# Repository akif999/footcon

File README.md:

# Footcon

Footcon is a USB device that send keyboard-like keys to a PC with a foot pedal.

## Hardware

The hardware composition is based on References 1. (Japanese website).  

Composition detail is below:

* Housing
    * TAKACHI YM-100
* Substrate
    * [footcon](https://github.com/akif999/footcon/tree/main/kicad/footcon)
    * [gerber](https://github.com/akif999/footcon/tree/main/gerber)
        * A board can be made using the files in this folder
* Foot pedal
    * [YAMAHA FC-5](https://jp.yamaha.com/products/music_production/accessories/fc5/index.html)
* Microcontroller board
    * [Seeed Studio XIAO SAMD21](https://lab.seeed.co.jp/entry/2022/08/19/120000)

## Software

The software consists of the following two items:

* Firmware
    * Software to detect pedal input and send key to PC
        * Write to XIAO
* Config GUI
    * Software for setting up Footcon
        * Works standalone on PC

### Firmware

Build and use the tinygo project under [firmware](https://github.com/akif999/footcon/tree/main/firmware).  

```
$ cd firmware
$ tinygo flash -target=xiao
```

* Requirement
    * Tinygo 0.27 or later

### Config GUI(WIP)

**Configuration GUI will be implemented as soon as Tinygo0.28.0 is released.**

Build [config_gui](https://github.com/akif999/footcon/tree/main/config_gui) and below to create an executable and use it.

```
$ cd config_gui
$ go build -o config_gui
$ ./config_gui
```

* Requirement
    * Go 1.19 or later

## References

1. https://qiita.com/carcon999/items/9b57537cadbfd3c13cf0

## License

This project is licensed under the MIT license.

## Author

Akifumi Kitabatake (a.k.a akif or akif999)

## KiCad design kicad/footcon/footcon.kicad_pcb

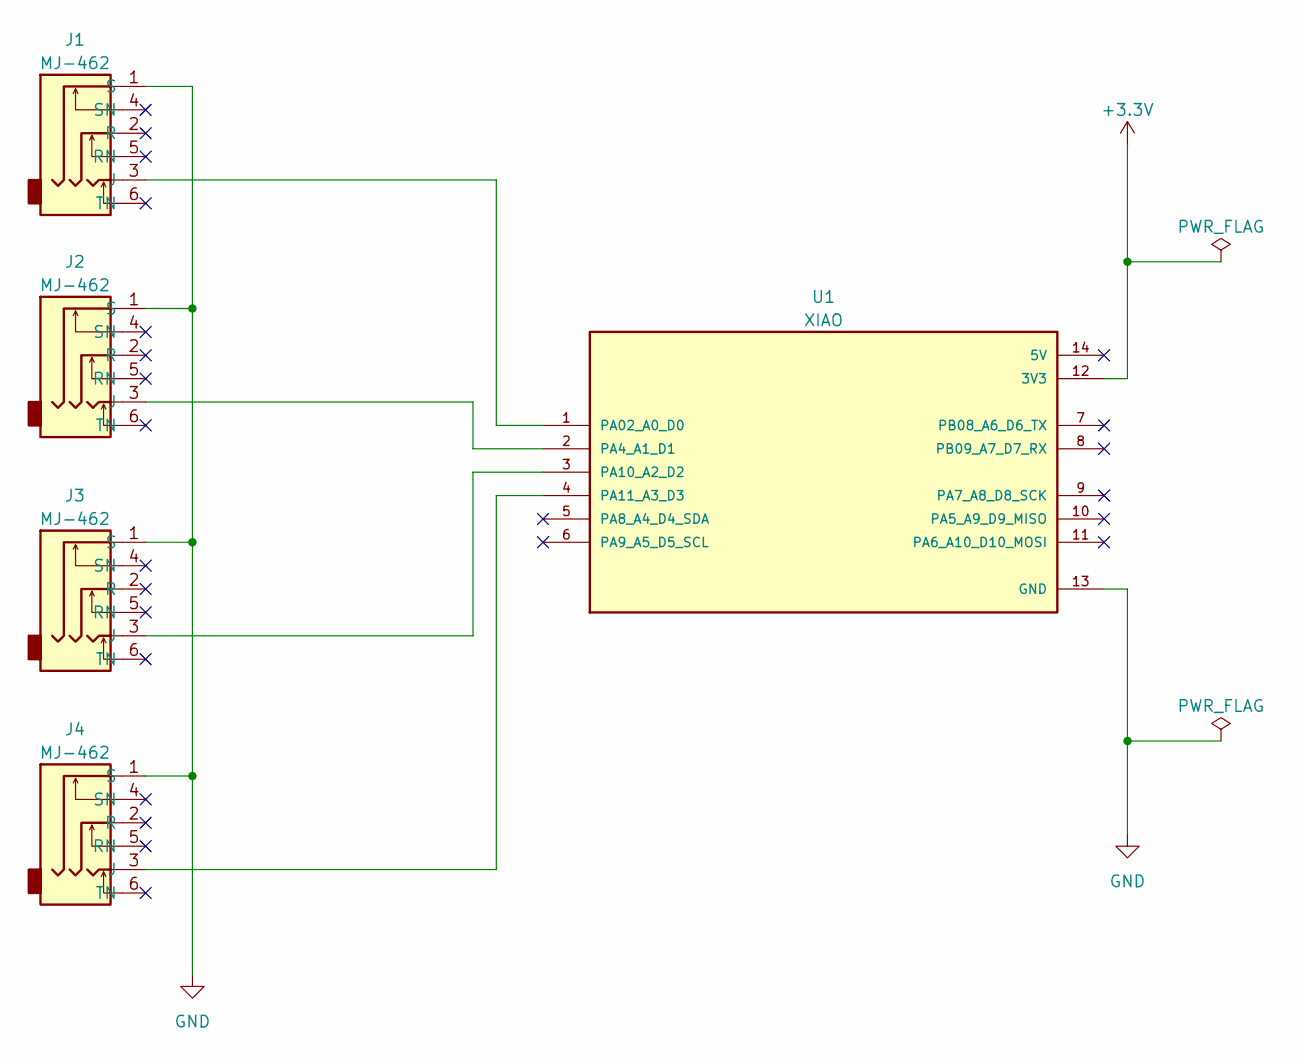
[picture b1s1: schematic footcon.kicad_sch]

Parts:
J1, J2, J3, J4: MJ-462
U1: XIAO; MODULE_102010388; PARTREV N/A

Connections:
+3.3V: U1.12 (3V3)
GND: J1.1 (S), J2.1 (S), J3.1 (S), J4.1 (S), U1.13 (GND)
unnamed: J1.3 (J), U1.1 (PA02_A0_D0)
unnamed: J2.3 (J), U1.2 (PA4_A1_D1)
unnamed: J3.3 (J), U1.3 (PA10_A2_D2)
unnamed: J4.3 (J), U1.4 (PA11_A3_D3)

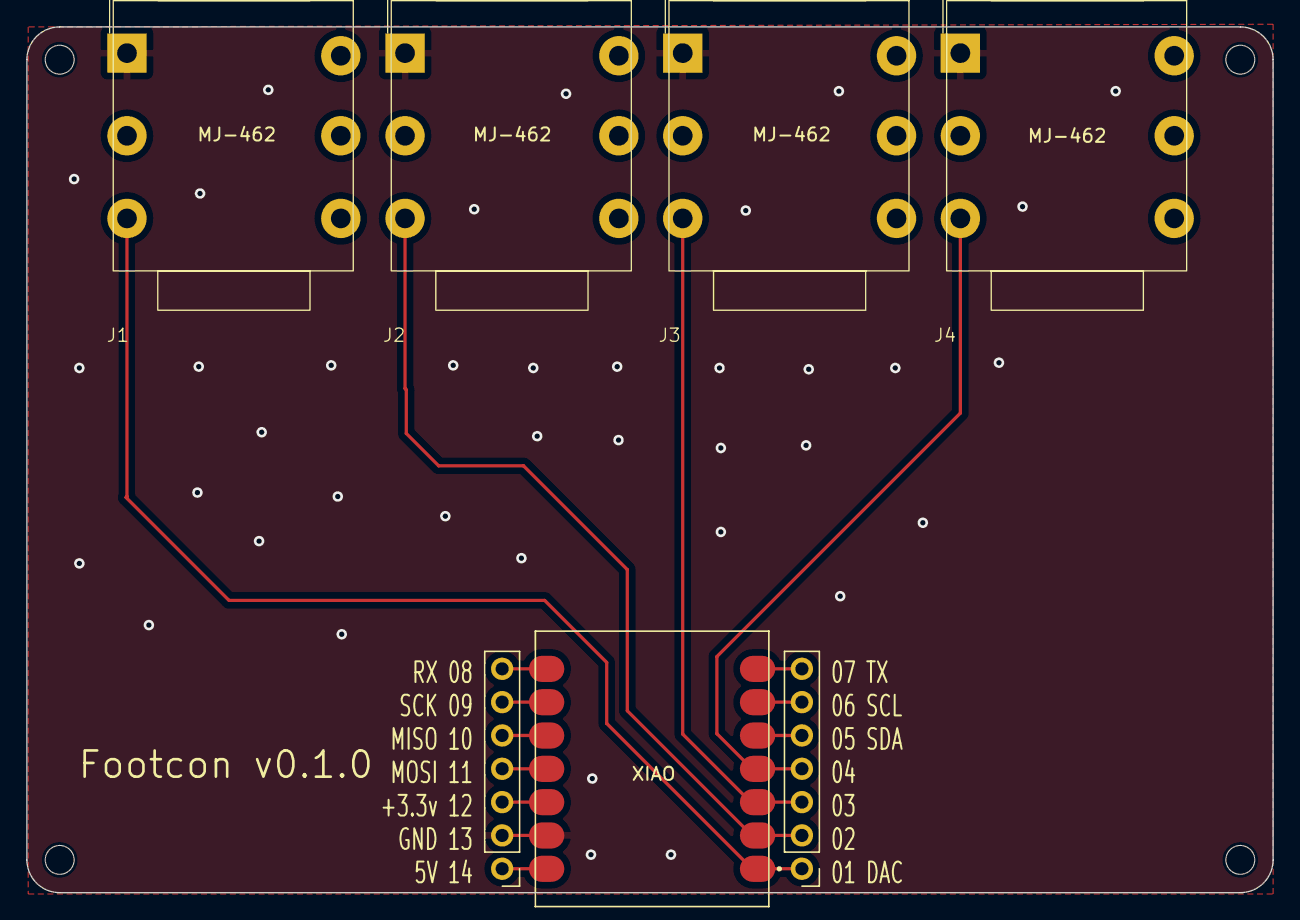
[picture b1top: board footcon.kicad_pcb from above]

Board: 2 copper layers, 95.0 x 66.0 mm, 5 parts (0 on the bottom side), 5 nets.

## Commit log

2023-02-27 Initial
2023-02-27 add libraries & add circuit diagram
2023-02-27 add pcb
2023-02-28 add unit name to front slikscreen
2023-02-28 add .gitignore
2023-03-07 add gerber files
2023-03-07 add easy example for firmware
2023-03-07 update prototype of firmware
2023-03-08 add README.md
2023-03-09 add keycode struct
